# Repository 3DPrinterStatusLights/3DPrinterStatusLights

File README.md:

# ECE 4180 - Design Project
## 3D Printer Status Lights - Invention Studio @ Georgia Tech

### Group Memebers
* Brandon Redder
* Seth Peden
* Dylan Mauldin
* Jacob Southerland

### Purpose
* The invention studio has 30 3D printers
* They are each controlled by a web management system with Raspberry PI’s
* There is no easy way to physically see the statuses of the printers

### Hardware
* Each printer is already connected to a Raspberry Pi v3
* The status lights are ShiftBrite SPI LEDs (shift registers)
* Each printer has one light connected to it
* Initial designs for the project utilized discrete RGB LEDs or an alternate microcontroller (with embedded RGB LED)

### Software
* The lights are controlled using the PIGPIO C++ library
* Status data is pulled from a pre-existing cloud service called 3D Printer OS
* Data from 3D Printer OS is retrieved within a JSON format from their REST API

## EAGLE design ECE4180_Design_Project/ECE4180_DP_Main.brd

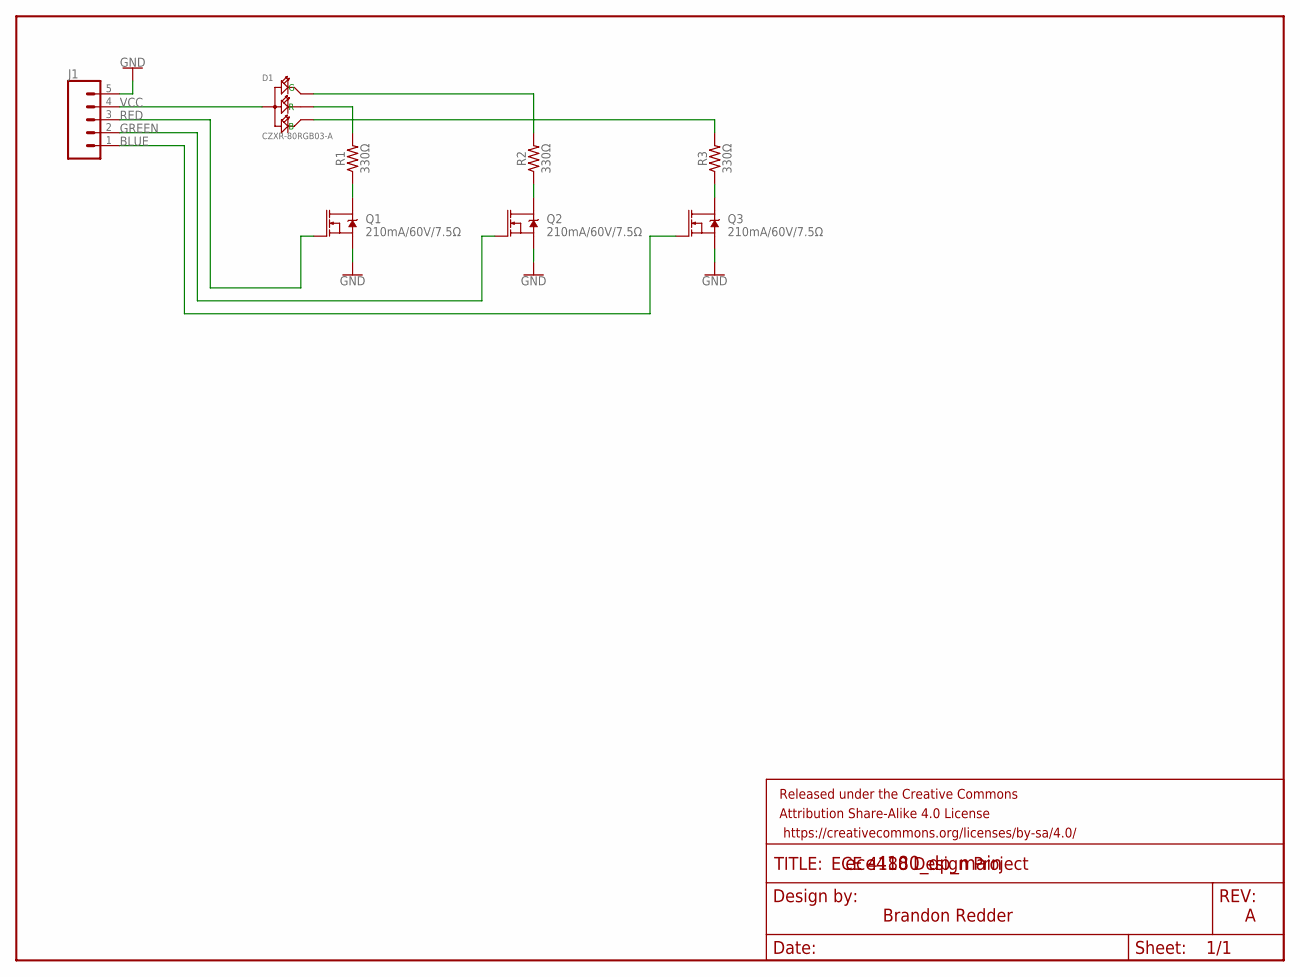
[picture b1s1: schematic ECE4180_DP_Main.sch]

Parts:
D1: CZXR-80RGB03-A; LED4-2.0-D8.0MM
FRAME: FRAME-LETTERNO_PACKAGE; DUMMY
J1: CONN_05LOCK; 1X05_LOCK
Q1, Q2, Q3: 210mA/60V/7.5Ω; SOT23-3
R1, R2, R3: 330Ω; 0805

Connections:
BLUE: J1.1, Q3.1 (G)
GND: J1.5, Q1.2 (S), Q2.2 (S), Q3.2 (S)
GREEN: J1.2, Q2.1 (G)
unnamed: D1.1 (R), R1.2
unnamed: D1.4 (B), R3.2
unnamed: D1.3 (G), R2.2
unnamed: Q1.3 (D), R1.1
unnamed: Q2.3 (D), R2.1
unnamed: Q3.3 (D), R3.1
RED: J1.3, Q1.1 (G)
VCC: D1.2 (+), J1.4

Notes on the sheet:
ECE 4180 Design Project
Brandon Redder

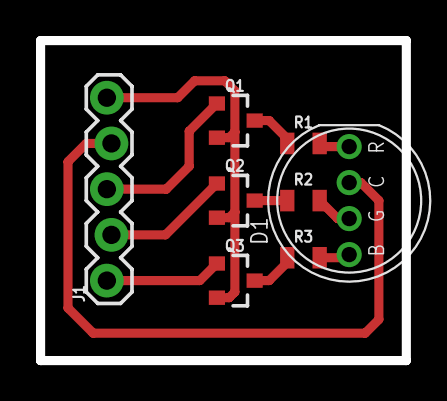
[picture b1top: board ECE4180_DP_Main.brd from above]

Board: 2 copper layers, 20.3 x 17.8 mm, 9 parts (0 on the bottom side), 11 nets.

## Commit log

2018-12-13 Pushed to public repository.
2018-12-13 Commented code.

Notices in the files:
parts and their libraries:
SparkFun-Aesthetics: Licensing: Creative Commons ShareAlike 4.0 International - https://creativecommons.org/licenses/by-sa/4.0
SparkFun-Aesthetics: Released under the Creative Commons Attribution Share-Alike 4.0 License
SparkFun-Aesthetics: https://creativecommons.org/licenses/by-sa/4.0
